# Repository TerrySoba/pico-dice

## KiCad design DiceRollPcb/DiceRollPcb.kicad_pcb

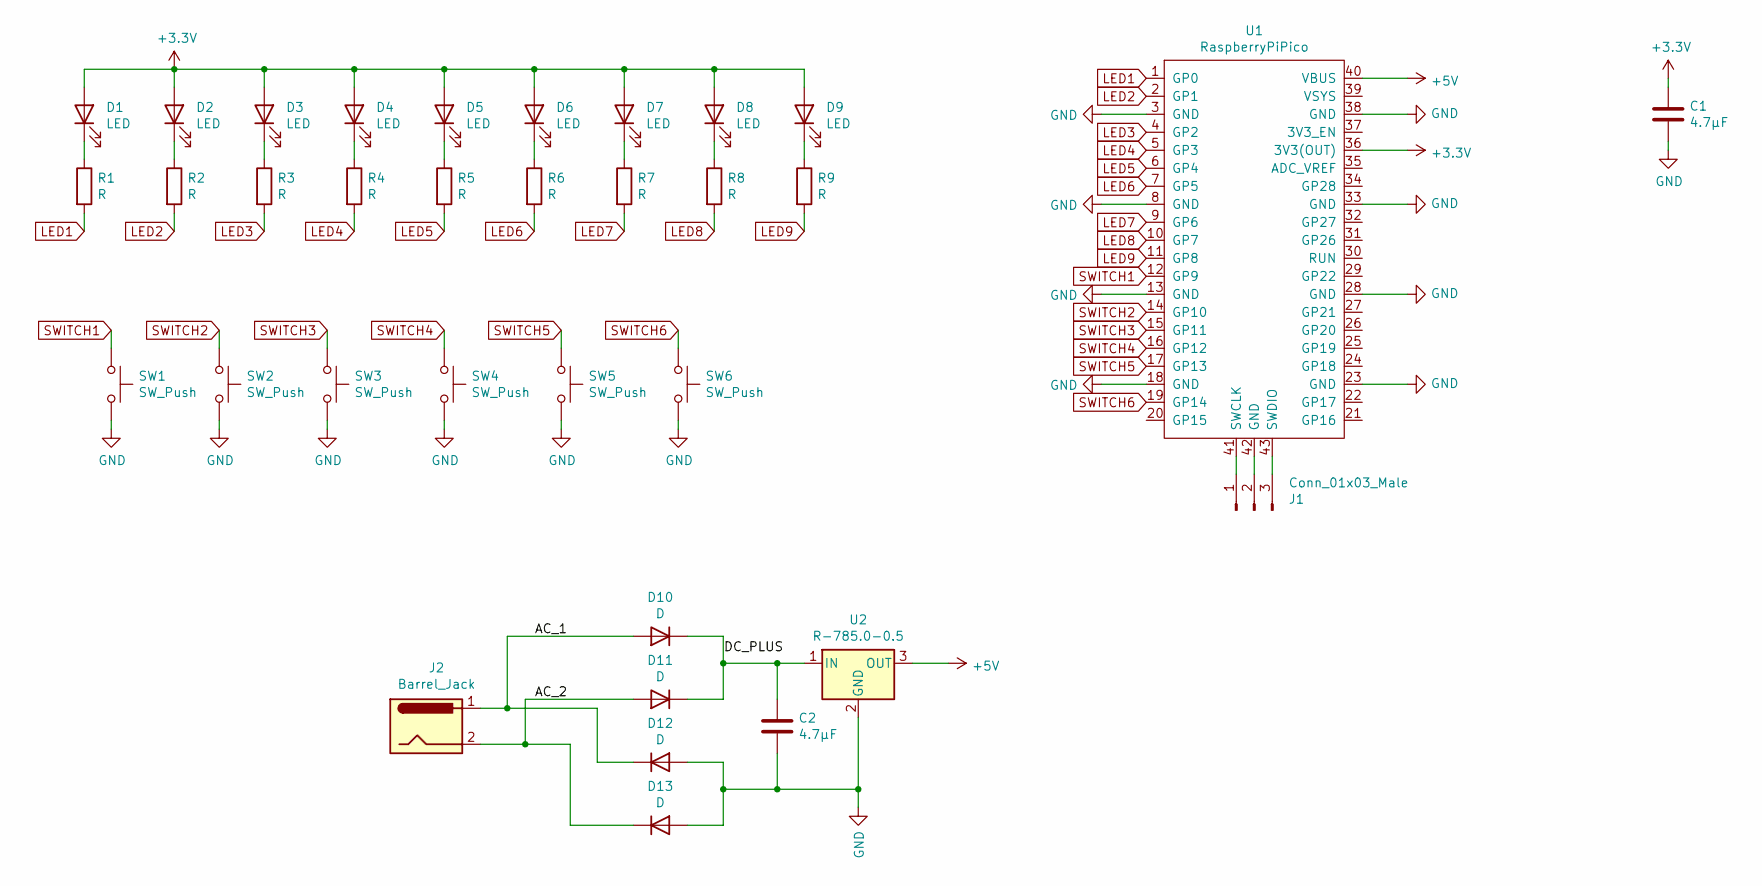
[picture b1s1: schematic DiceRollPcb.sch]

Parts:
C1, C2: 4.7µF; C_Disc_D4.3mm_W1.9mm_P5.00mm
D1, D2, D3, D4, D5, D6, D7, D8, D9: LED; LED_D5.0mm
D10, D11, D12, D13: D; D_5W_P12.70mm_Horizontal
J1: Conn_01x03_Male; PinHeader_1x03_P2.54mm_Vertical
J2: Barrel_Jack; BarrelJack_Horizontal
R1, R2, R3, R4, R5, R6, R7, R8, R9: R; R_Axial_DIN0207_L6.3mm_D2.5mm_P10.16mm_Horizontal
SW1, SW2, SW3, SW4, SW5, SW6: SW_Push; SW_PUSH_6mm
U1: RaspberryPiPico; RPi_Pico_SMD_TH
U2: R-785.0-0.5; Converter_DCDC_RECOM_R-78E-0.5_THT

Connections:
+3V3: C1.1, D1.2 (A), D2.2 (A), D3.2 (A), D4.2 (A), D5.2 (A), D6.2 (A), D7.2 (A), D8.2 (A), D9.2 (A), U1.36 (3V3(OUT))
+5V: U1.40 (VBUS), U2.3 (OUT)
/AC_1: D10.2 (A), D12.1 (K), J2.1
/AC_2: D11.2 (A), D13.1 (K), J2.2
/DC_PLUS: C2.1, D10.1 (K), D11.1 (K), U2.1 (IN)
GND: C1.2, C2.2, D12.2 (A), D13.2 (A), SW1.2, SW2.2, SW3.2, SW4.2, SW5.2, SW6.2, U1.3 (GND), U1.8 (GND), U1.13 (GND), U1.18 (GND), U1.23 (GND), U1.28 (GND), U1.33 (GND), U1.38 (GND), U2.2 (GND)
LED1: R1.2, U1.1 (GP0)
LED2: R2.2, U1.2 (GP1)
LED3: R3.2, U1.4 (GP2)
LED4: R4.2, U1.5 (GP3)
LED5: R5.2, U1.6 (GP4)
LED6: R6.2, U1.7 (GP5)
LED7: R7.2, U1.9 (GP6)
LED8: R8.2, U1.10 (GP7)
LED9: R9.2, U1.11 (GP8)
unnamed: D1.1 (K), R1.1
unnamed: D2.1 (K), R2.1
unnamed: D3.1 (K), R3.1
unnamed: D4.1 (K), R4.1
unnamed: D5.1 (K), R5.1
unnamed: D6.1 (K), R6.1
unnamed: D7.1 (K), R7.1
unnamed: D8.1 (K), R8.1
unnamed: D9.1 (K), R9.1
unnamed: J1.1, U1.41 (SWCLK)
unnamed: J1.2, U1.42 (GND)
unnamed: J1.3, U1.43 (SWDIO)
SWITCH1: SW1.1, U1.12 (GP9)
SWITCH2: SW2.1, U1.14 (GP10)
SWITCH3: SW3.1, U1.15 (GP11)
SWITCH4: SW4.1, U1.16 (GP12)
SWITCH5: SW5.1, U1.17 (GP13)
SWITCH6: SW6.1, U1.19 (GP14)

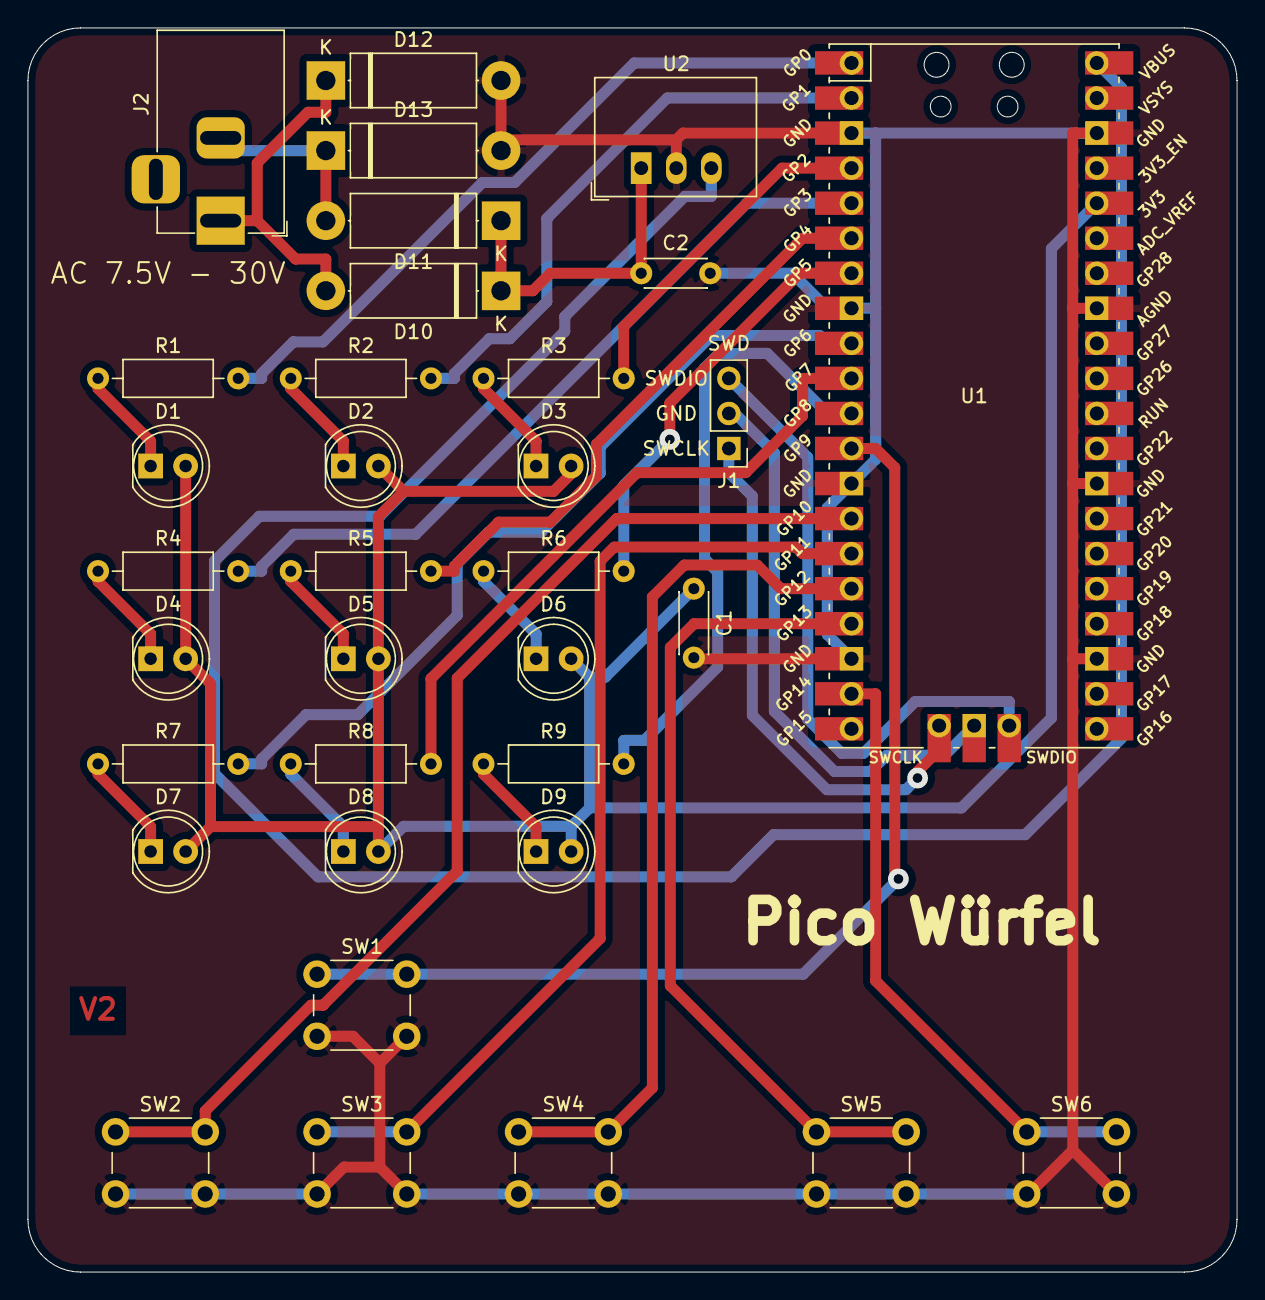
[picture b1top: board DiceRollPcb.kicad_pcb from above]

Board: 2 copper layers, 87.6 x 90.2 mm, 34 parts (0 on the bottom side), 33 nets.

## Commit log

2021-02-28 Version 2
